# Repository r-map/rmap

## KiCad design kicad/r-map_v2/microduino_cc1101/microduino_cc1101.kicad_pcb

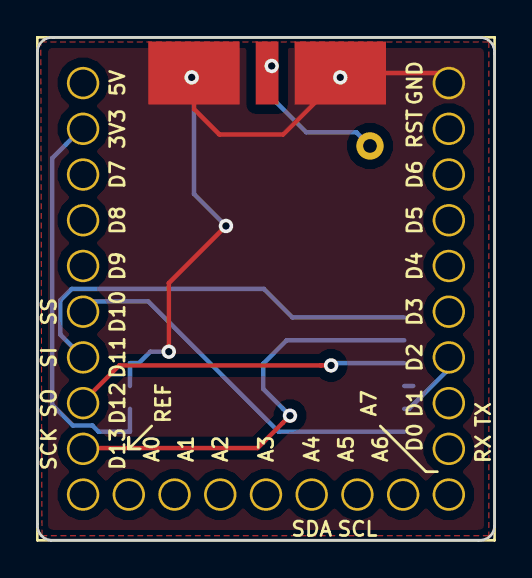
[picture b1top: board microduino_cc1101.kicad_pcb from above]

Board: 2 copper layers, 25.4 x 27.9 mm, 3 parts (1 on the bottom side), 8 nets.

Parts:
J1: Conn_Coaxial; SMA_EDGE
U1: Microduino; microduino
U2: CC1101-868MHz-Module

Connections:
+3V3: U1.26, U2.7, U2.8
GDO0: U1.7, U2.5
GND: J1.2, U1.1, U2.9, U2.10
MISO: U1.20, U2.3
MOSI: U1.21, U2.1
unnamed: J1.1, U2.ANT
SCLK: U1.19, U2.2
SS: U1.22, U2.6

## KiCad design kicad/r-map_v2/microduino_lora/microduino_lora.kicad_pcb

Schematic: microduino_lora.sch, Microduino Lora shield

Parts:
J1: Conn_Coaxial; SMA_EDGE
J2, J3, J4, J5: Conn_01x01; Measurement_Point_Round-SMD-Pad_Small
U1: Microduino; microduino
U2: RFM95

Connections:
+3V3: U1.26 (3V3), U2.13
FSKTimeOut: J5.1, U2.16
GND: J1.2 (Ext), U1.1 (GND), U2.1, U2.8, U2.10
MISO: U1.20 (D12), U2.2
MOSI: U1.21 (D11), U2.3
NSS: U1.22 (D10), U2.5
unnamed: J1.1 (In), U2.9
unnamed: J2.1, U1.10 (A7)
unnamed: J4.1, U1.11 (A6)
RST: U1.14 (A3), U2.6
RxTimeOut: J3.1, U2.15
SCK: U1.19 (D13), U2.4
TxRxDONE: U1.7 (D2), U2.14

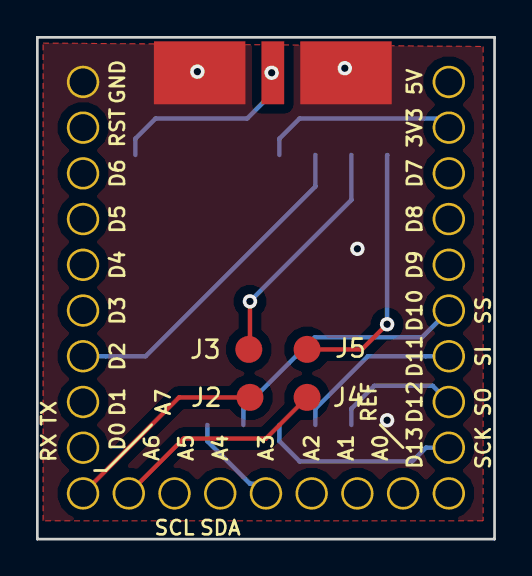
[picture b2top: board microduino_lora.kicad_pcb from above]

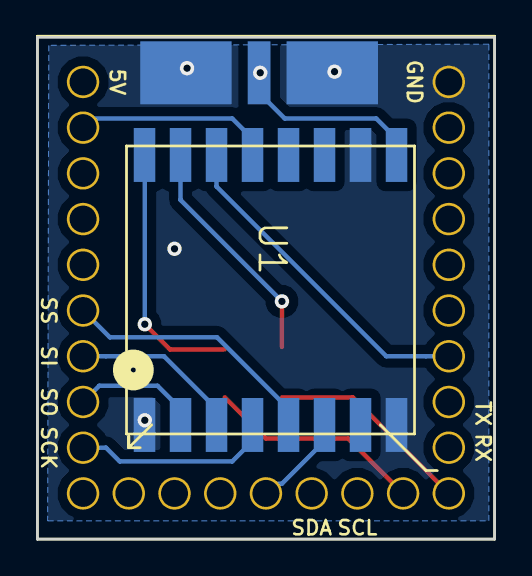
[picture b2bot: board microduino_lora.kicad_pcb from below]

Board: 2 copper layers, 25.4 x 27.9 mm, 7 parts (2 on the bottom side), 13 nets.

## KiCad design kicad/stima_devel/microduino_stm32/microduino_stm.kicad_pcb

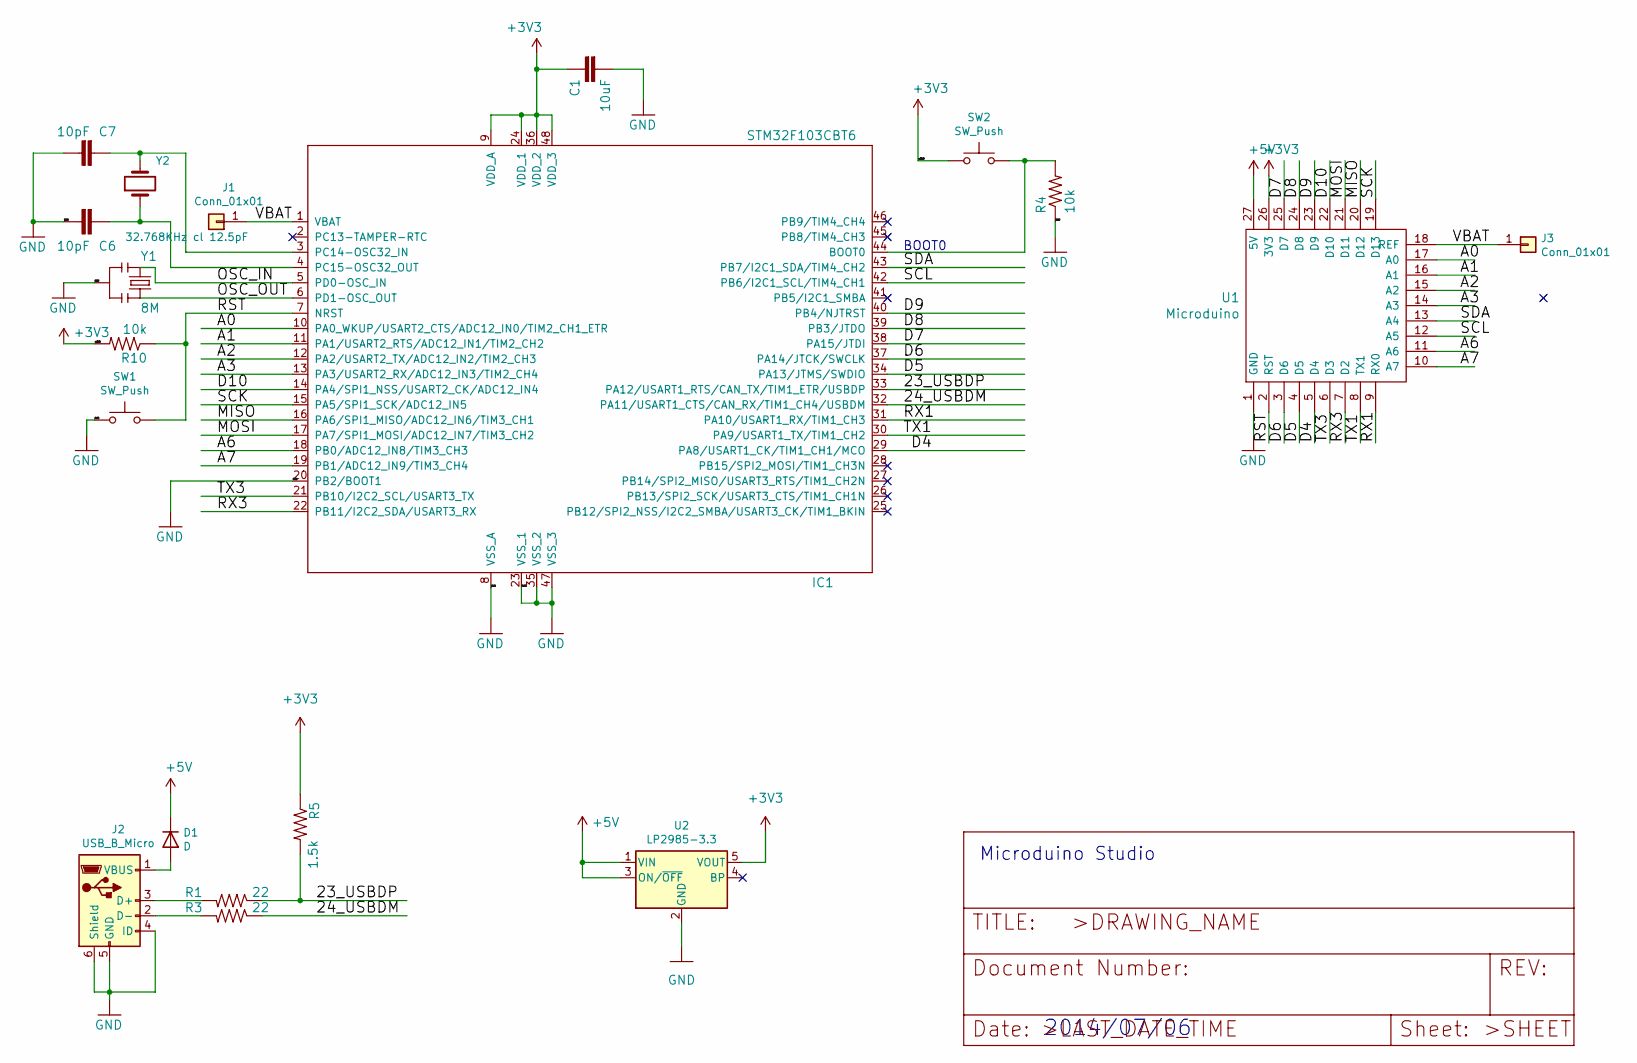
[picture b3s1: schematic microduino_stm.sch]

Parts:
C1: 10uF; C_0805_2012Metric
C6, C7: 10pF; C_0603_1608Metric
D1: D; STPS0530Z
IC1: STM32F103CBT6; LQFP-48_7x7mm_P0.5mm
J1, J3: Conn_01x01; TestPoint_Pad_1.0x1.0mm
J2: USB_B_Micro; USB_Micro-B_GCT_USB3076-30-A
R1, R3: 22; R_0805_2012Metric
R4, R10: 10k; R_0805_2012Metric
R5: 1.5k; R_0805_2012Metric
SW1, SW2: SW_Push; SW_Push_1P1T_NO_CK_KMR2
U1: Microduino; microduino
U2: LP2985-3.3; SOT-23-5
Y1: 8M; Resonator_SMD_muRata_CSTxExxV-3Pin_3.0x1.1mm
Y2: 32.768KHz cl 12.5pF; Crystal_SMD_EuroQuartz_EQ161-2Pin_3.2x1.5mm

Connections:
+3V3: C1.1, IC1.9 (VDD_A), IC1.24 (VDD_1), IC1.36 (VDD_2), IC1.48 (VDD_3), R5.1, R10.2, SW2.1, U1.26 (3V3), U2.5 (VOUT)
+5V: D1.1 (K), U1.27 (5V), U2.1 (VIN), U2.3 (ON/~OFF~)
/23_USBDP: IC1.33 (PA12/USART1_RTS/CAN_TX/TIM1_ETR/USBDP), R1.1, R5.2
/24_USBDM: IC1.32 (PA11/USART1_CTS/CAN_RX/TIM1_CH4/USBDM), R3.1
/A0: IC1.10 (PA0_WKUP/USART2_CTS/ADC12_IN0/TIM2_CH1_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), U1.17 (A0)
/A1: IC1.11 (PA1/USART2_RTS/ADC12_IN1/TIM2_CH2), U1.16 (A1)
/A2: IC1.12 (PA2/USART2_TX/ADC12_IN2/TIM2_CH3), U1.15 (A2)
/A3: IC1.13 (PA3/USART2_RX/ADC12_IN3/TIM2_CH4), U1.14 (A3)
/A6: IC1.18 (PB0/ADC12_IN8/TIM3_CH3), U1.11 (A6)
/A7: IC1.19 (PB1/ADC12_IN9/TIM3_CH4), U1.10 (A7)
/D4: IC1.29 (PA8/USART1_CK/TIM1_CH1/MCO), U1.5 (D4)
/D5: IC1.34 (PA13/JTMS/SWDIO), U1.4 (D5)
/D6: IC1.37 (PA14/JTCK/SWCLK), U1.3 (D6)
/D7: IC1.38 (PA15/JTDI), U1.25 (D7)
/D8: IC1.39 (PB3/JTDO), U1.24 (D8)
/D9: IC1.40 (PB4/NJTRST), U1.23 (D9)
/D10: IC1.14 (PA4/SPI1_NSS/USART2_CK/ADC12_IN4), U1.22 (D10)
/MISO: IC1.16 (PA6/SPI1_MISO/ADC12_IN6/TIM3_CH1), U1.20 (D12)
/MOSI: IC1.17 (PA7/SPI1_MOSI/ADC12_IN7/TIM3_CH2), U1.21 (D11)
/OSC_IN: IC1.5 (PD0-OSC_IN), Y1.1
/OSC_OUT: IC1.6 (PD1-OSC_OUT), Y1.3
/RST: IC1.7 (NRST), R10.1, SW1.2, U1.2 (RST)
/RX1: IC1.31 (PA10/USART1_RX/TIM1_CH3), U1.9 (RX0)
/RX3: IC1.22 (PB11/I2C2_SDA/USART3_RX), U1.7 (D2)
/SCK: IC1.15 (PA5/SPI1_SCK/ADC12_IN5), U1.19 (D13)
/SCL: IC1.42 (PB6/I2C1_SCL/TIM4_CH1), U1.12 (A5)
/SDA: IC1.43 (PB7/I2C1_SDA/TIM4_CH2), U1.13 (A4)
/TX1: IC1.30 (PA9/USART1_TX/TIM1_CH2), U1.8 (TX1)
/TX3: IC1.21 (PB10/I2C2_SCL/USART3_TX), U1.6 (D3)
/VBAT: IC1.1 (VBAT), J1.1, J3.1, U1.18 (REF)
GND: C1.2, C6.1, C7.1, IC1.8 (VSS_A), IC1.20 (PB2/BOOT1), IC1.23 (VSS_1), IC1.35 (VSS_2), IC1.47 (VSS_3), J2.4 (ID), J2.5 (GND), J2.6 (Shield), R4.1, SW1.1, U1.1 (GND), U2.2 (GND), Y1.2
unnamed: C6.2, IC1.4 (PC15-OSC32_OUT), Y2.1
unnamed: C7.2, IC1.3 (PC14-OSC32_IN), Y2.2
unnamed: D1.2 (A), J2.1 (VBUS)
unnamed: IC1.44 (BOOT0), R4.2, SW2.2
unnamed: J2.2 (D-), R3.2
unnamed: J2.3 (D+), R1.2

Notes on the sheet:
BOOT0
Microduino Studio
2014/07/06

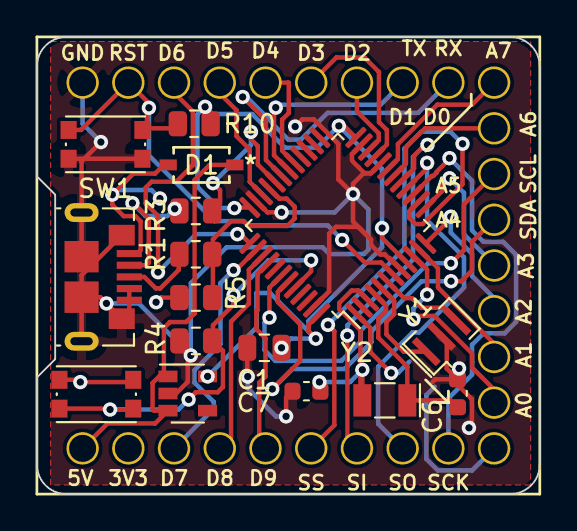
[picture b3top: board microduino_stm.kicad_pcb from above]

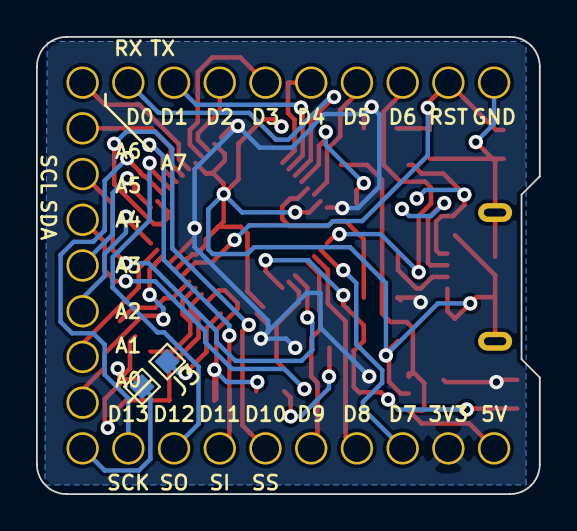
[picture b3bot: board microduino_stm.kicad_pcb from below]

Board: 2 copper layers, 27.9 x 25.4 mm, 19 parts (2 on the bottom side), 37 nets.

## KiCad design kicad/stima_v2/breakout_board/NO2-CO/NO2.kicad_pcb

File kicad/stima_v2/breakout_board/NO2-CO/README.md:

Schematic preview
=================

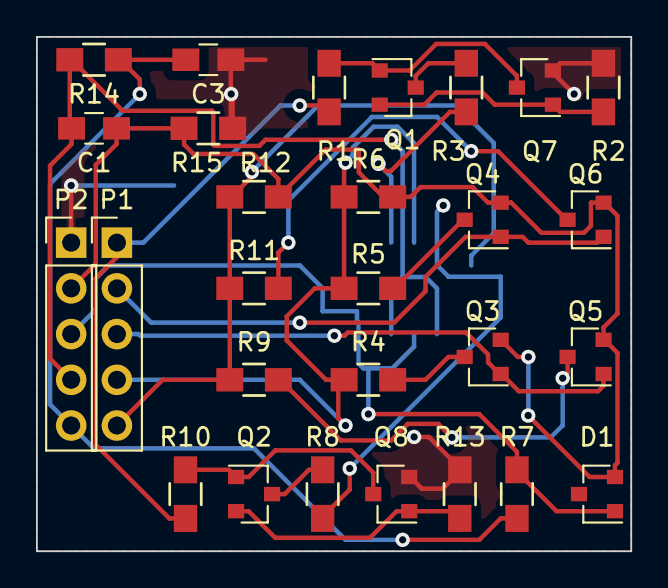
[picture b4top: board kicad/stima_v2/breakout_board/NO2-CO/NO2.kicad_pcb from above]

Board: 2 copper layers, 33.0 x 28.6 mm, 29 parts (1 on the bottom side), 22 nets.

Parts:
C1, C3: 22u; C_0805_HandSoldering
D1: ZENER; SOT-23
P1, P2: CONN_01X05; Pin_Header_Straight_1x05_Pitch2.54mm
Q1, Q2, Q3, Q4, Q5, Q6: 2N7002; SOT-23
Q7, Q8: BC849; SOT-23
R1, R10: 47k; R_0805_HandSoldering
R2: 21R5; R_0805_HandSoldering
R3: 75; R_0805_HandSoldering
R4, R9: 10K; R_0805_HandSoldering
R5, R11: 100K; R_0805_HandSoldering
R6, R12: 1M; R_0805_HandSoldering
R7: 560; R_0805_HandSoldering
R8: 47; R_0805_HandSoldering
R13: 17R4; R_0805_HandSoldering
R14, R15: 100; R_0805_HandSoldering
U1: MICS-4514

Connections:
+5V: C3.1, P2.5, R7.1, R14.2
CO: P1.4, R4.1, R5.1, R6.1, U1.B
GND: C3.2, P2.1, Q7.2, Q8.2, R2.2, R13.2, R15.2
GNDD: C1.2, D1.2, P2.2, Q3.2, Q4.2, Q5.2, Q6.2, R6.2, R12.2, R15.1
NO2: P1.5, R9.1, R11.1, R12.1, U1.D
unnamed: Q1.1, Q7.3, R1.2
unnamed: Q1.2, Q7.1, R2.1
unnamed: Q1.3, R3.2
unnamed: Q2.1, Q8.3, R10.2
unnamed: Q2.2, Q8.1, R13.1
unnamed: Q2.3, R8.2
unnamed: Q3.3, R4.2
unnamed: Q4.3, R5.2
unnamed: Q5.3, R9.2
unnamed: Q6.3, R11.2
unnamed: R3.1, U1.A
unnamed: R8.1, U1.C
PWM: P1.1, R1.1, R10.1
SCALE_1: P1.2, Q4.1, Q6.1
SCALE_2: P1.3, Q3.1, Q5.1
VDD: C1.1, P2.4, R14.1, U1.F, U1.H
VREF: D1.1, P2.3, R7.2, U1.G, U1.J

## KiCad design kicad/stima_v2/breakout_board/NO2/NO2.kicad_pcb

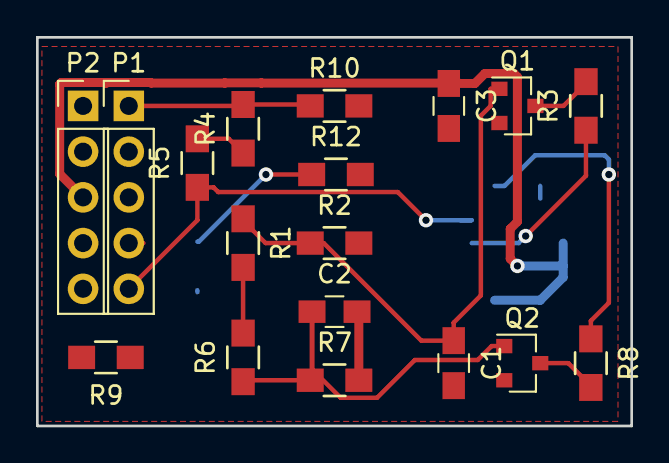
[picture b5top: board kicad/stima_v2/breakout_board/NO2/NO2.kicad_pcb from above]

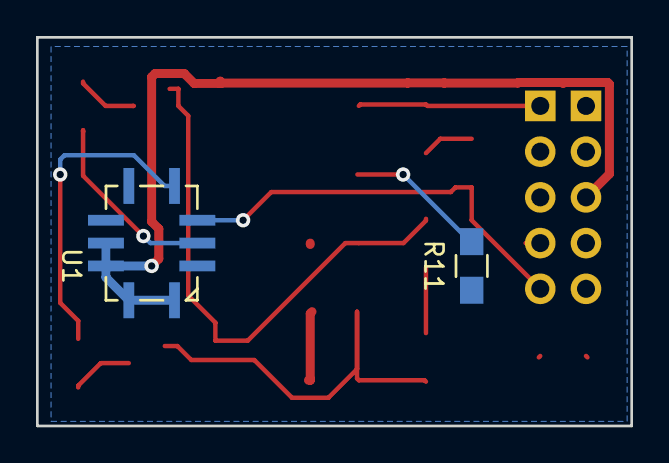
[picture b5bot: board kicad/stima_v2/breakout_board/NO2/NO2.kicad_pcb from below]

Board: 2 copper layers, 33.0 x 21.6 mm, 20 parts (2 on the bottom side), 15 nets.

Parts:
C1, C2: 10n; C_0805_HandSoldering
C3: C; C_0805_HandSoldering
P1, P2: CONN_01X05; Pin_Header_Straight_1x05_Pitch2.54mm
Q1, Q2: 2N7002; SOT-23
R1, R6: 330; R_0805_HandSoldering
R2, R5, R7, R9: 10K; R_0805_HandSoldering
R3: 75R; R_0805_HandSoldering
R4, R11: 100K; R_0805_HandSoldering
R8: R82; R_0805_HandSoldering
R10, R12: 1M; R_0805_HandSoldering
U1: MICS-4514

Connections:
+5V: C3.1, P2.3, U1.7, U1.8, U1.9, U1.10
/FET_DRIVE: C2.1, Q2.1, R6.1, R7.1
CO: P1.4, R9.1, U1.5
CO_SCALE_1: P1.2, R9.2, R11.1
CO_SCALE_2: P1.3, R11.2, R12.1
FET: P2.4, R1.2, R6.2
GND: C1.2, C2.2, C3.2, P2.2, Q1.2, Q2.2, R2.2, R7.2, R10.2, R12.2
NO2: P1.5, R5.1, U1.3
NO2_SCALE_1: P2.5, R4.1, R5.2
NO2_SCALE_2: P1.1, R4.2, R10.1
unnamed: C1.1, Q1.1, R1.1, R2.1
unnamed: Q1.3, R3.2
unnamed: Q2.3, R8.2
unnamed: R3.1, U1.2
unnamed: R8.1, U1.4

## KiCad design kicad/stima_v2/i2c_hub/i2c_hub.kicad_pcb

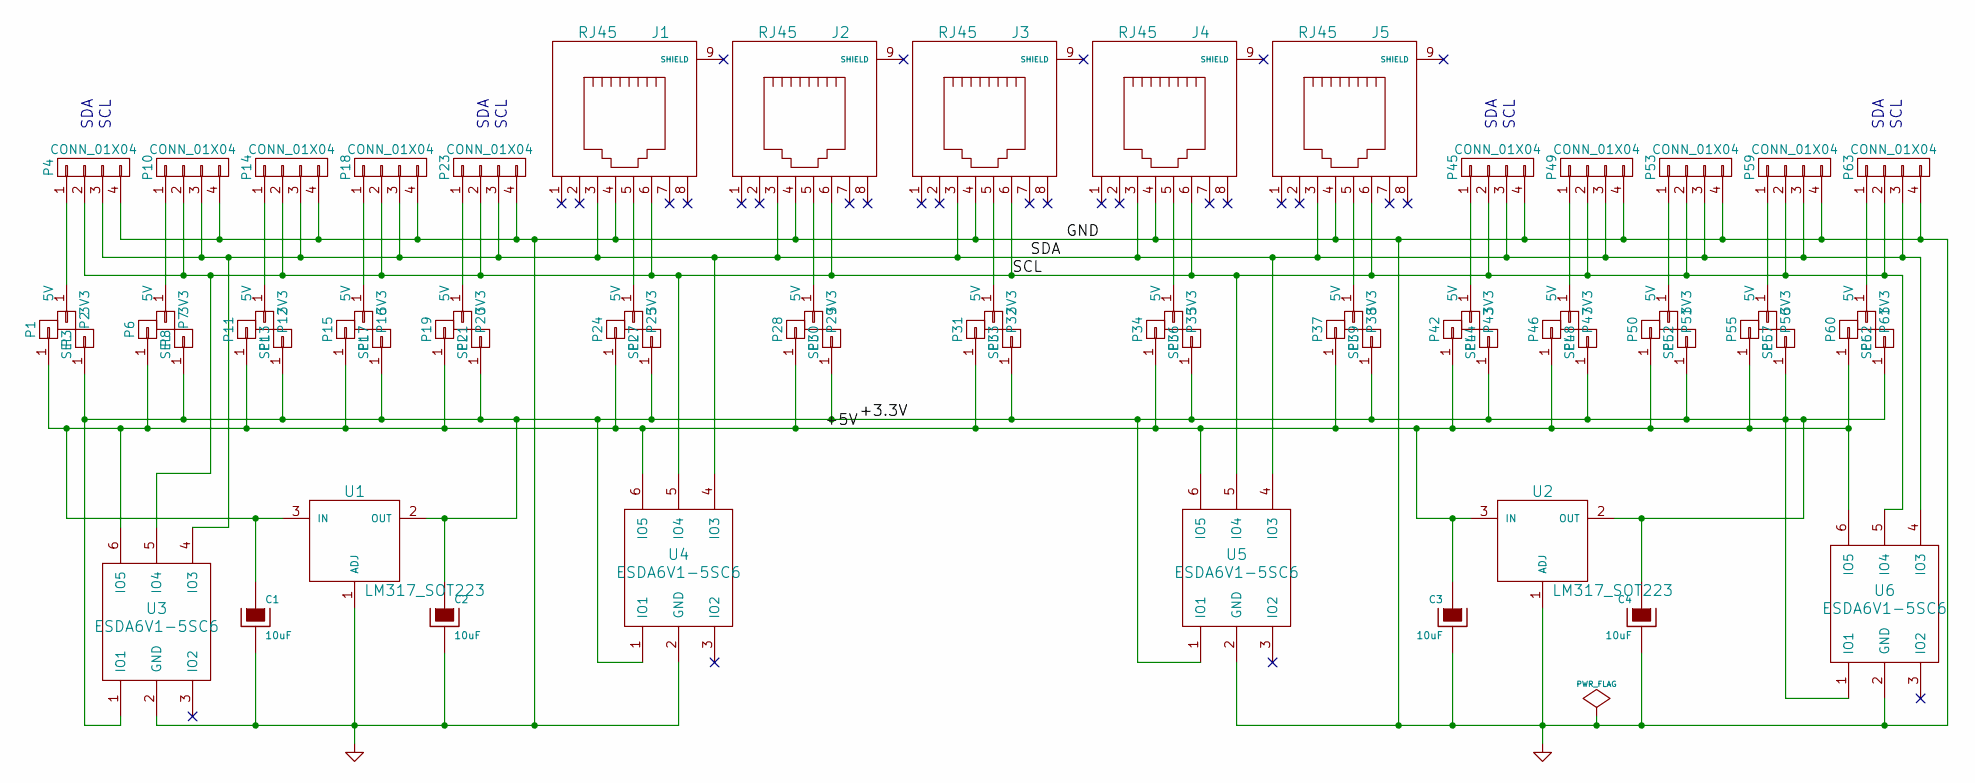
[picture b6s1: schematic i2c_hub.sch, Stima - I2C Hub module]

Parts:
C1, C2, C3, C4: 10uF; c_1206
J1, J2, J3, J4, J5: RJ45; RJ45_8
P1, P6, P11, P15, P19, P24, P28, P31, P34, P37, P42, P46, P50, P55, P60: 5V; Measurement_Point_Round-SMD-Pad_Small
P2, P7, P12, P16, P20, P25, P29, P32, P35, P38, P43, P47, P51, P56, P61: SEL; Measurement_Point_Round-SMD-Pad_Small
P3, P8, P13, P17, P21, P27, P30, P33, P36, P39, P44, P48, P52, P57, P62: 3V3; Measurement_Point_Round-SMD-Pad_Small
P4, P10, P14, P18, P23, P45, P49, P53, P59, P63: CONN_01X04; pin_strip_4
U1, U2: LM317_SOT223; sot223
U3, U4, U5, U6: ESDA6V1-5SC6; sot23-6

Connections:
/+3.3V: C2.1, C4.1, P3.1, P8.1, P13.1, P17.1, P21.1, P27.1, P30.1, P33.1, P36.1, P39.1, P44.1, P48.1, P52.1, P57.1, P62.1, U1.2 (OUT), U2.2 (OUT), U3.1 (IO1), U4.1 (IO1), U5.1 (IO1), U6.1 (IO1)
/+5V: C1.1, C3.1, P1.1, P6.1, P11.1, P15.1, P19.1, P24.1, P28.1, P31.1, P34.1, P37.1, P42.1, P46.1, P50.1, P55.1, P60.1, U1.3 (IN), U2.3 (IN), U3.6 (IO5), U4.6 (IO5), U5.6 (IO5), U6.6 (IO5)
/SCL: J1.6, J2.6, J3.6, J4.6, J5.6, P4.2, P10.2, P14.2, P18.2, P23.2, P45.2, P49.2, P53.2, P59.2, P63.2, U3.5 (IO4), U4.5 (IO4), U5.5 (IO4), U6.5 (IO4)
/SDA: J1.3, J2.3, J3.3, J4.3, J5.3, P4.3, P10.3, P14.3, P18.3, P23.3, P45.3, P49.3, P53.3, P59.3, P63.3, U3.4 (IO3), U4.4 (IO3), U5.4 (IO3), U6.4 (IO3)
GND: C1.2, C2.2, C3.2, C4.2, J1.4, J2.4, J3.4, J4.4, J5.4, P4.4, P10.4, P14.4, P18.4, P23.4, P45.4, P49.4, P53.4, P59.4, P63.4, U1.1 (ADJ), U2.1 (ADJ), U3.2 (GND), U4.2 (GND), U5.2 (GND), U6.2 (GND)
unnamed: J1.5, P25.1
unnamed: J2.5, P29.1
unnamed: J3.5, P32.1
unnamed: J4.5, P35.1
unnamed: J5.5, P38.1
unnamed: P2.1, P4.1
unnamed: P7.1, P10.1
unnamed: P12.1, P14.1
unnamed: P16.1, P18.1
unnamed: P20.1, P23.1
unnamed: P43.1, P45.1
unnamed: P47.1, P49.1
unnamed: P51.1, P53.1
unnamed: P56.1, P59.1
unnamed: P61.1, P63.1

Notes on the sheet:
SDA
SCL

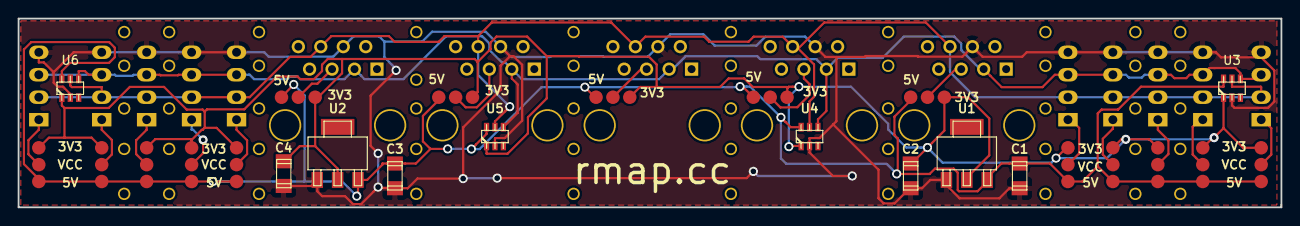
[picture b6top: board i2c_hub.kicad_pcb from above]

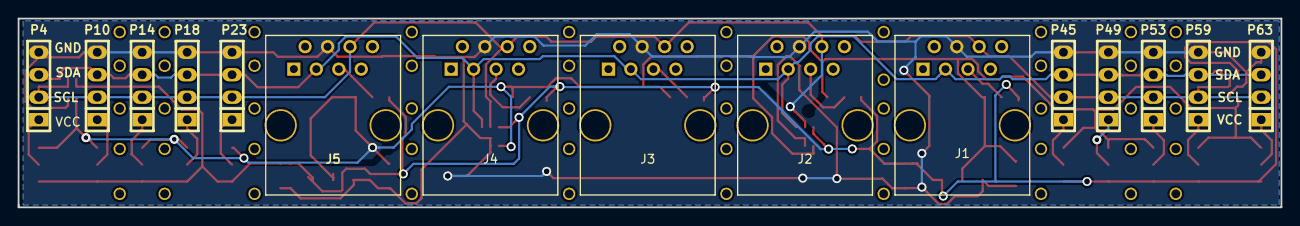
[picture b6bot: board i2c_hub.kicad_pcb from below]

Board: 2 copper layers, 142.7 x 21.3 mm, 70 parts (15 on the bottom side), 20 nets.

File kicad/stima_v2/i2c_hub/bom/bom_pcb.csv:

Item,Reference(s),Value,Quantity,Package,Esempio
1,C1 C2 C3 C4,10uF,4,1206 smd,
2,J1 J2 J3 J4 J5,RJ45,5,connettore RJ45 non schermato,
3,P1 P11 P15 P19 P24 P28 P31 P34 P37 P42 P46 P50 P55 P6 P60,5V,15,piazzola senza componenti,
4,P10 P14 P18 P23 P4 P45 P49 P53 P59 P63,CONN_01X04,10,strip connector maschio 4 pin,
5,P12 P16 P2 P20 P25 P29 P32 P35 P38 P43 P47 P51 P56 P61 P7,SEL,15,piazzola senza componenti,
6,P13 P17 P21 P27 P3 P30 P33 P36 P39 P44 P48 P52 P57 P62 P8,3V3,15,piazzola senza componenti,
7,U1 U2,LM1117-3.3,2,SOT-223 smd,
8,U3 U4 U5 U6,ESDA6V1-5SC6,4,SOT23-6 smd,http://it.farnell.com/stmicroelectronics/esda6v1-5sc6/transi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

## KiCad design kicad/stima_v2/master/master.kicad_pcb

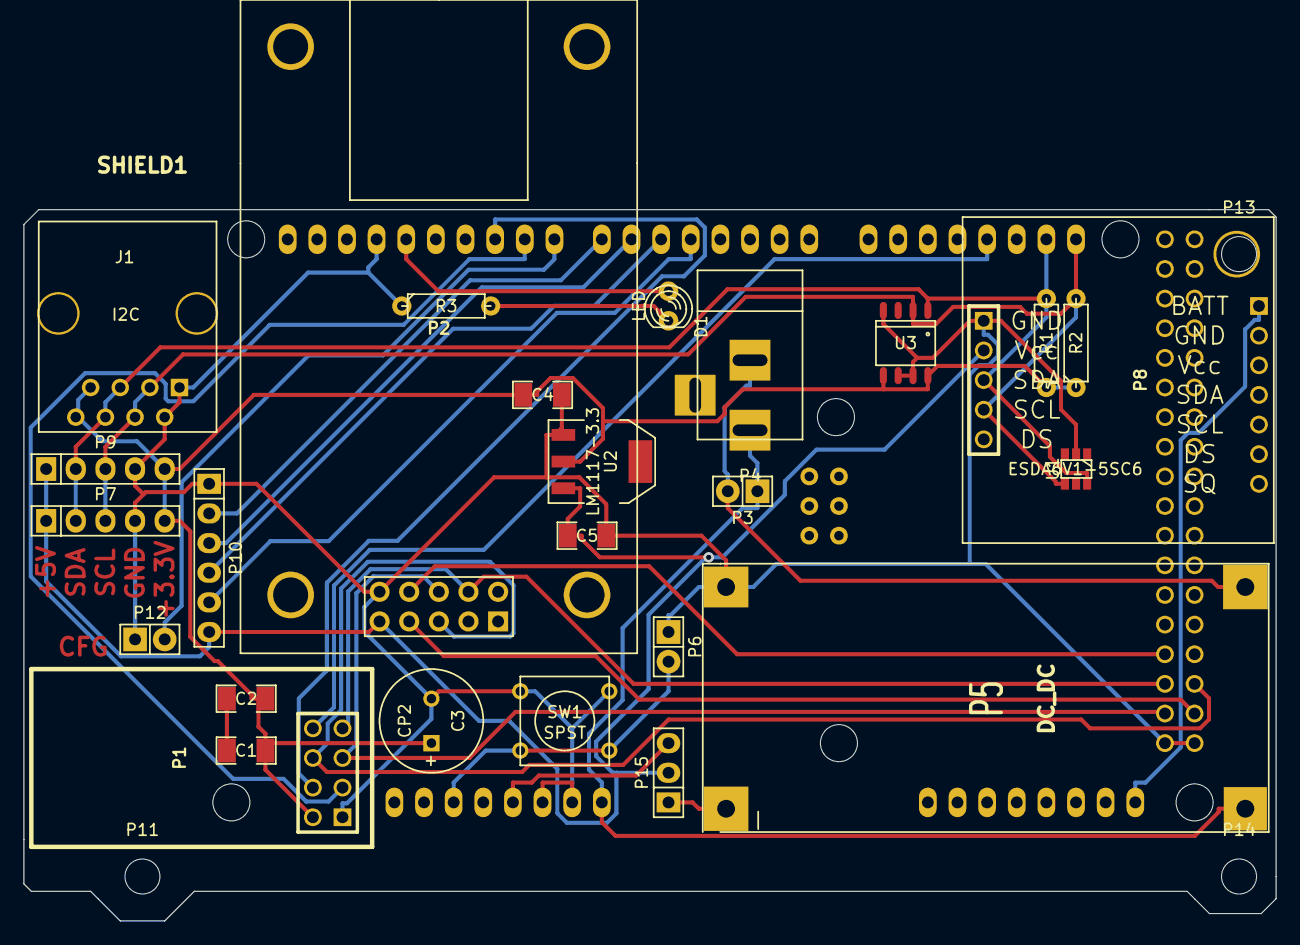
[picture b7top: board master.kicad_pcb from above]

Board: 2 copper layers, 107.3 x 61.0 mm, 30 parts (0 on the bottom side), 27 nets.

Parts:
C1: CP2; SMD-1206
C2, C4, C5: C; SMD-1206
C3: CP2; C1.5V8V
D1: LED; LED-3MM
J1: I2C; RJ45_8
P1: NRF24L01_BRD; NRF24L01
P2: ENC28J60_BRD; ENC28J60_capovolto
P3, P6: CONN_01X02; Pin_Header_Straight_1x02
P4: CONN_01X03; BARREL_JACK
P5: DC_DC
P7, P9: CONN_01X05; Pin_Header_Straight_1x05
P8: RTC; RTC_0I2C_AT24C32_DS1307_capovolto
P10: CONN_01X06; Pin_Header_Straight_1x06
P11, P13, P14: CONN_01X01; MountingHole_3mm
P12: CONFIG; Pin_Header_Straight_1x02
P15: CONN_01X03; Pin_Header_Straight_1x03
R1, R2, R3: R; R3-LARGE_PADS
SHIELD1: ARDUINO_MEGA_SHIELD
SW1: SPST; SW_PUSH_SMALL
U1: ESDA6V1-5SC6; SOT-23-6
U2: LM1117-3.3; SOT-223
U3: TMP275; SO-8

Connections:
GND: C3.2, C4.2, C5.2, J1.1, J1.2, P1.1, P2.10, P5.4, P6.1, P7.4, P8.1, P9.4, P10.1, P12.1, R3.1, SHIELD1.GND1, SHIELD1.GND2, SHIELD1.GND3, SHIELD1.GND4, SHIELD1.GND5, SW1.1, U1.2, U2.1, U3.4, U3.6, U3.7
unnamed: C1.1, C2.1, C3.1, C4.1, J1.7, J1.8, P1.2, P7.5, P9.5, R1.1, R2.1, U2.2, U3.5, U3.8
unnamed: C1.2, C2.2
unnamed: C5.1, P2.9, P7.1, P8.2, P9.1, P10.6, P15.2, U2.3
unnamed: D1.1, SHIELD1.13
unnamed: D1.2, R3.2
unnamed: J1.3, J1.4, P7.3, P8.4, P9.3, R2.2, SHIELD1.21, U1.4, U3.2
unnamed: J1.5, J1.6, P7.2, P8.3, P9.2, R1.2, SHIELD1.20, U1.6, U3.1
unnamed: P1.3, SHIELD1.9
unnamed: P1.4, SHIELD1.10
unnamed: P1.5, P2.6, SHIELD1.52
unnamed: P1.6, P2.5, SHIELD1.51
unnamed: P1.7, P2.4, SHIELD1.50
unnamed: P1.8, SHIELD1.18
unnamed: P2.7, SHIELD1.53
unnamed: P2.8, SHIELD1.48
unnamed: P3.1, P4.1, P5.1, SHIELD1.V_IN
unnamed: P3.2, P4.2, P5.2
unnamed: P6.2, SHIELD1.RST, SW1.2
unnamed: P8.6, SHIELD1.AD15
unnamed: P10.2, SHIELD1.7
unnamed: P10.3, SHIELD1.6
unnamed: P10.4, SHIELD1.5
unnamed: P10.5, SHIELD1.4
unnamed: P12.2, SHIELD1.8
unnamed: P5.3, P15.1
unnamed: P15.3, SHIELD1.5V

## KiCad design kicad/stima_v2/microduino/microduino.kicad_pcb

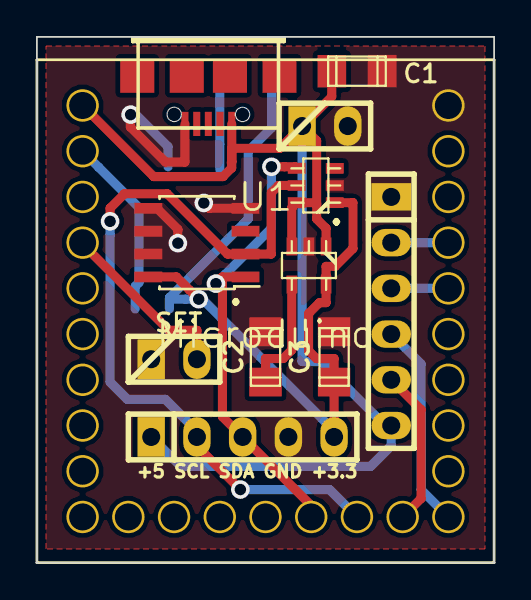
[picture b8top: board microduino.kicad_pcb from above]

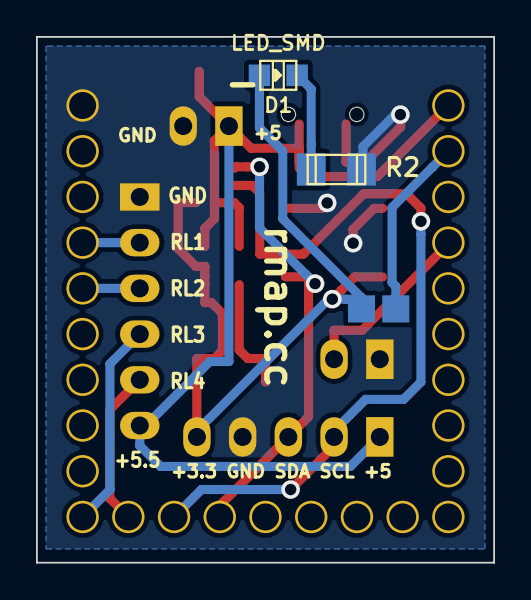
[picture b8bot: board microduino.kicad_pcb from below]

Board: 2 copper layers, 25.4 x 29.2 mm, 16 parts (4 on the bottom side), 13 nets.

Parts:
C1: 1uF; c_1206
C2: 0.01uF; c_1206
C3: 2.2uF; c_1206
D1: LED_SMD; Led_0805
P1: CONN_01X02; pin_strip_2
P2: CONN_RELE_BOARD; pin_strip_6
P3: CONN_01X05; pin_strip_5
P4: CONFIG; pin_strip_2
P5: USB_OTG; conn_usb_B_micro_smd-2
P6, P7: CONN_01X01; Measurement_Point_Square-SMD-Pad_Small
R2: 820; r_1206
U1: Microduino; microduino
U2: ESDA6V1-5SC6; sot23-6
U3: REG113NA-3.3/250; sot23-5
U4: TMP275; SOIC-8_3.9x4.9mm_Pitch1.27mm

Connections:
/+3.3V: C3.1, D1.1, P3.5, P7.1, U2.1, U3.5, U4.8
/+5V: C1.1, P1.1, P2.6, P3.1, P5.1, U1.27, U2.6, U3.1, U3.3
/SCL: P3.2, U1.12, U2.5, U4.2
/SDA: P3.3, U1.13, U2.4, U4.1
GND: C1.2, C2.2, C3.2, P1.2, P2.1, P3.4, P4.1, P5.5, R2.2, U1.1, U2.2, U3.2, U4.4, U4.5, U4.6, U4.7
unnamed: C2.1, U3.4
unnamed: D1.2, R2.1
unnamed: P2.2, U1.4
unnamed: P2.3, U1.5
unnamed: P2.4, U1.10
unnamed: P2.5, U1.11
unnamed: P4.2, U1.24
unnamed: P6.1, U1.26

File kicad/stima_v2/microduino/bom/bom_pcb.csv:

Item,Reference(s),Value,Quantity
1,C1,1uF,1
2,C2,0.01uF,1
3,C3,2.2uF,1
4,D1,LED_SMD,1
5,P1,CONN_01X02,1
6,P2,CONN_RELE_BOARD,1
7,P3,CONN_01X05,1
8,P4,CONFIG,1
9,P5,USB_OTG,1
10,P6 P7,CONN_01X01,2
11,R2,150,1
12,U1,Microduino,1
13,U2,ESDA6V1-5SC6,1
14,U3,REG113NA-3.3/250,1
15,U4,TMP275,1

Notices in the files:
kicad/r-map_v2/i2c_hub/i2c_hub.sch:
Released under MIT License(MIT)
parts and their libraries:
Copyright 2016 Accelerated Designs. All rights reserved.
